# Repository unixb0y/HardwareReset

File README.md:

# HardwareReset

Allows you to completely cut power from a device under test using just a low-current logic signal from an FPGA or microcontroller.

Also an easy way to power a target from a lab bench PSU or other independent power supply without requiring adapters.

<sub>Created with KiCAD 8.0</sub>

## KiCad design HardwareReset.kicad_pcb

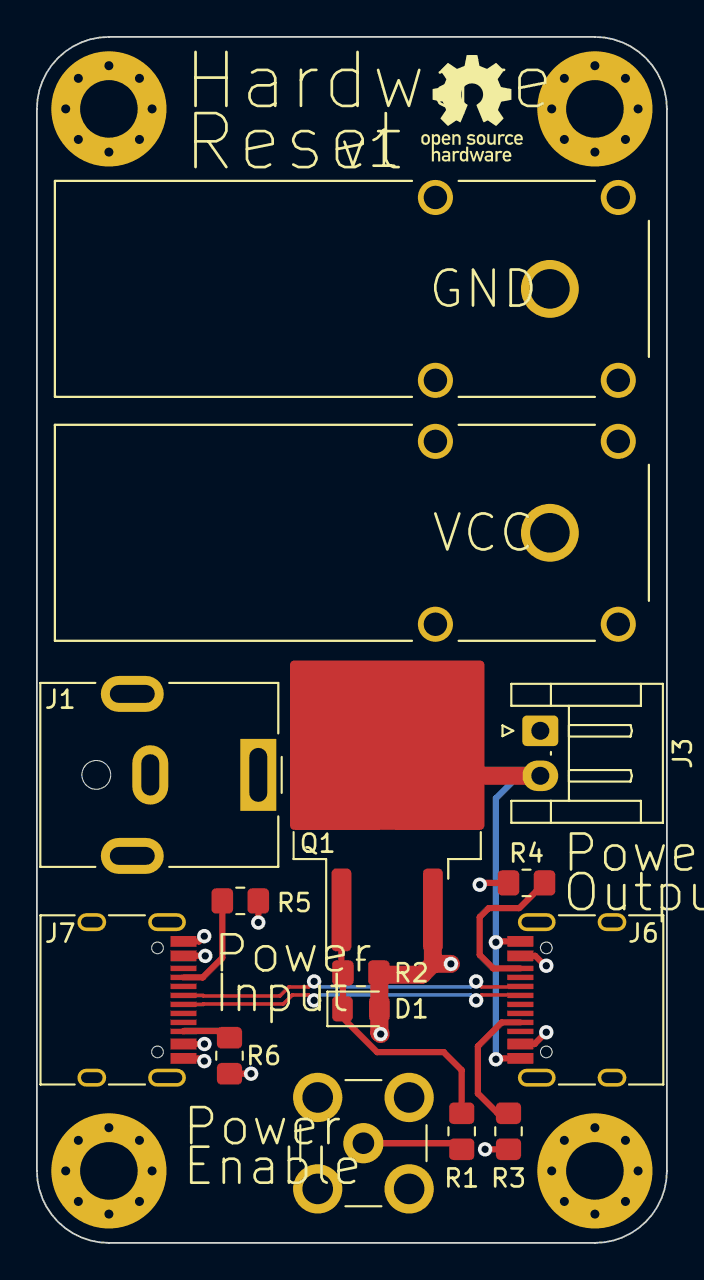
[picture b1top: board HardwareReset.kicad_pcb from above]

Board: 4 copper layers, 35.0 x 67.0 mm, 19 parts (0 on the bottom side), 11 nets.

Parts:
D1: D_Zener; D_0805_2012Metric_Pad1.15x1.40mm_HandSolder
H1: H1; MountingHole_3.2mm_M3_Pad_Via
H2: H2; MountingHole_3.2mm_M3_Pad_Via
H3: H3; MountingHole_3.2mm_M3_Pad_Via
H4: H4; MountingHole_3.2mm_M3_Pad_Via
J1: Barrel Jack; BarrelJack_CUI_PJ-063AH_Horizontal
J2: VCC; POMONA_73099-0
J3: Conn_01x02; JST_EH_S2B-EH_1x02_P2.50mm_Horizontal
J4: GND; POMONA_73099-0
J5: Conn_Coaxial; SMB_Jack_Vertical
J6, J7: USB_C_Receptacle_USB2.0; USB_C_Receptacle_HRO_TYPE-C-31-M-12
Q1: IRLZ44N; TO-263-2
R1: 200O; R_0805_2012Metric_Pad1.20x1.40mm_HandSolder
R2: 10K; R_0805_2012Metric_Pad1.20x1.40mm_HandSolder
R3, R4, R5, R6: 5.1k; R_0805_2012Metric_Pad1.20x1.40mm_HandSolder

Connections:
D+: J6.B6 (D+), J7.A6 (D+)
D-: J6.A7 (D-), J7.A7 (D-)
GND: D1.2 (A), H1.1, H2.1, H3.1, H4.1, J1.2, J4.1, J5.2 (Ext), J7.A1 (GND), J7.A12 (GND), J7.B1 (GND), J7.B12 (GND), Q1.3 (S), R2.2, R3.1, R4.1, R5.1, R6.1
MOSFET_EN: J5.1 (In), R1.2
unnamed: D1.1 (K), Q1.1 (G), R1.1, R2.1
unnamed: J6.A5 (CC1), R3.2
unnamed: J6.B5 (CC2), R4.2
unnamed: J7.A5 (CC1), R5.2
unnamed: J7.B5 (CC2), R6.2
TGT_GND: J3.2, J6.A1 (GND), J6.A12 (GND), J6.B1 (GND), J6.B12 (GND), Q1.2 (D)
VCC: J1.1, J2.1, J3.1, J6.A4 (VBUS), J6.A9 (VBUS), J6.B4 (VBUS), J6.B9 (VBUS), J7.A4 (VBUS), J7.A9 (VBUS), J7.B4 (VBUS), J7.B9 (VBUS)

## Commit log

2024-07-09 Add license
